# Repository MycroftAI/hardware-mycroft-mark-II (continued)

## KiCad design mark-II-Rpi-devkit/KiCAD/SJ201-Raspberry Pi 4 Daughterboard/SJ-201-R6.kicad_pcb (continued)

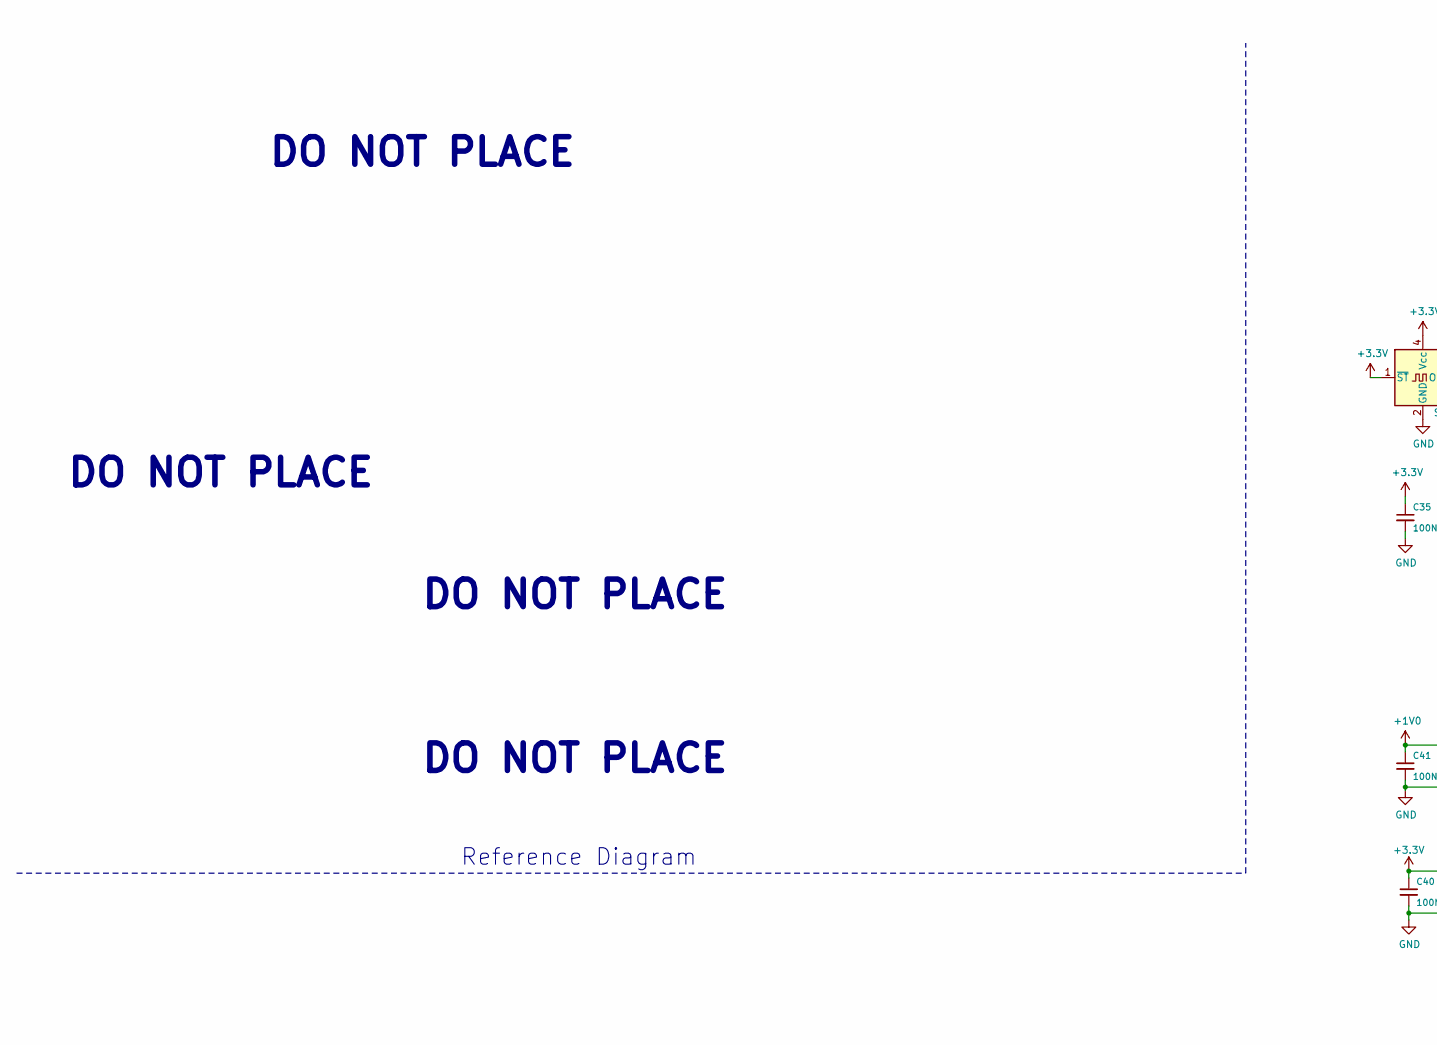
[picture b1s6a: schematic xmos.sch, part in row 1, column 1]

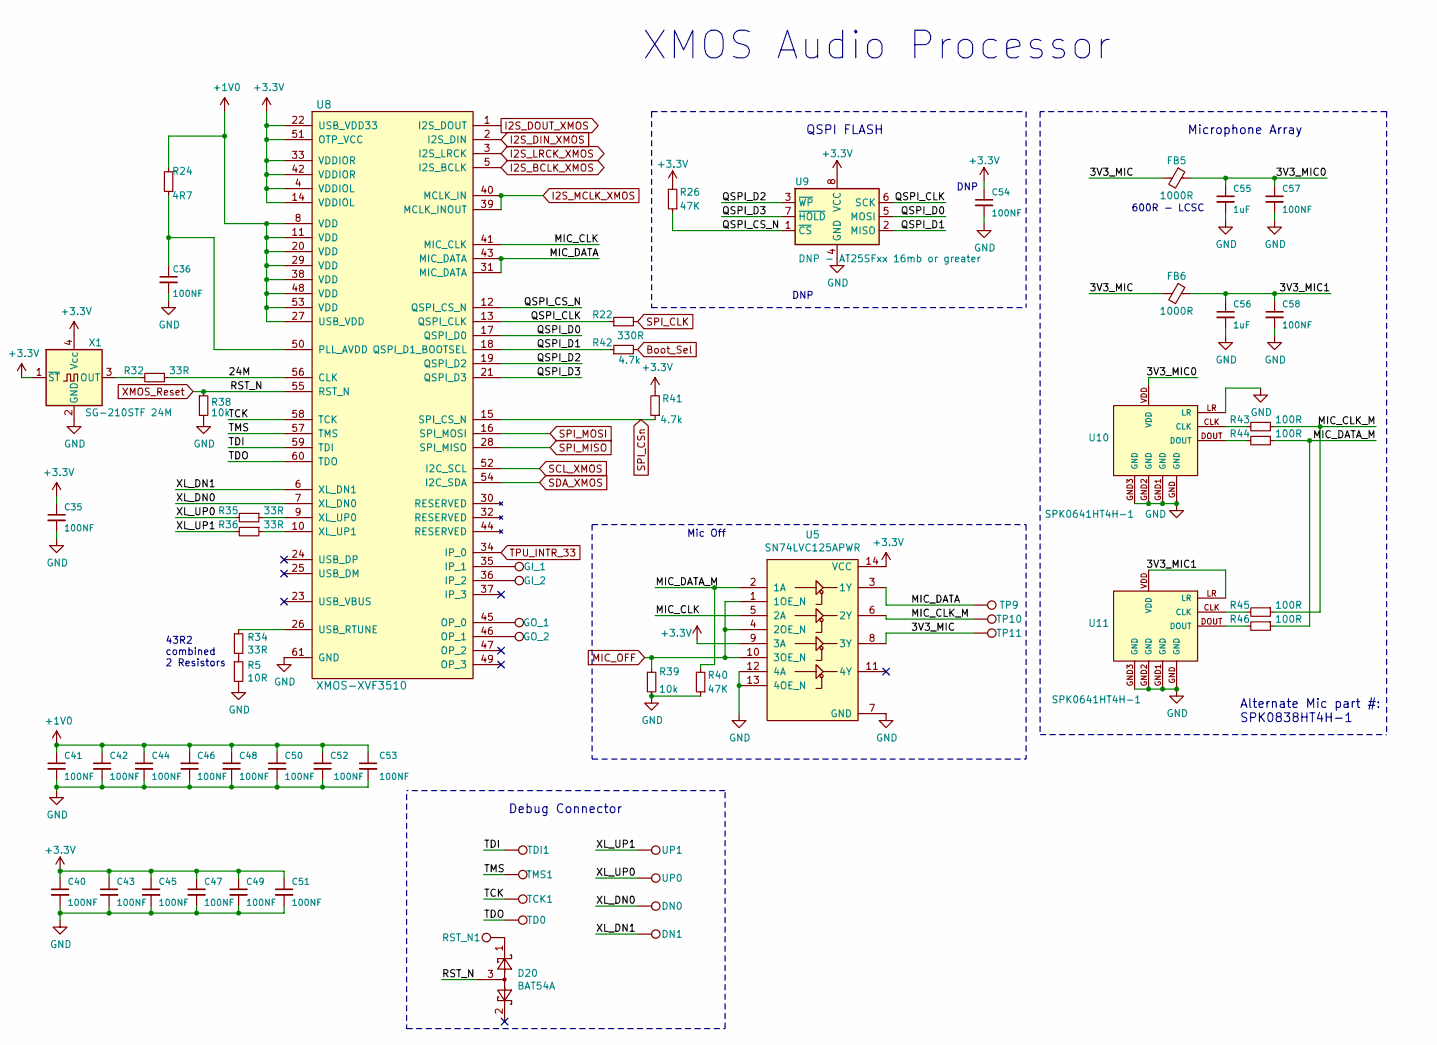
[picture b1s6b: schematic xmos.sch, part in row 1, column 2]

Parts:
C35, C36, C40, C41, C42, C43, C44, C45, C46, C47, C48, C49, C50, C51, C52, C53, C54, C57, C58: 100NF; C_0402_1005Metric; MPN CC0402KRX7R8BB104; LCSC C1525
C55, C56: 1uF; C_0402_1005Metric; MPN CL05A105KA5NQNC; LCSC C52923
D20: BAT54A; SOT-23; MPN BAT54ALT1G; LCSC C179724
DN0, DN1: TestPoint; TestPoint_Pad_D1.0mm; MPN DNP
FB5: 1000R; R_0805_2012Metric; MPN MPZ1608S102ATA00; LCSC C1017
FB6: 1000R; R_0805_2012Metric; PartNum MPZ1608S102ATA00; LCSC C1017
GI_1, GI_2: TestPoint; TestPoint_Pad_D2.0mm; MPN DNP
GO_1, GO_2: TestPoint; TestPoint_Pad_D2.0mm; MPN DNP
R5: 10R; R_0402_1005Metric; MPN 0402WGF100JTCE; LCSC C25077
R22: 330R; R_0402_1005Metric; MPN RC0402FR-07330RL; LCSC C25104
R24: 4R7; R_0603_1608Metric; MPN RC0402FR-074R7L; LCSC C23164
R26: 47K; R_0402_1005Metric; MPN 0402WGF4702TCE; LCSC C25792
R32, R34, R35, R36: 33R; R_0402_1005Metric; MPN 0402WGF330JTCE; LCSC C25105
R38, R39: 10k; R_0402_1005Metric; MPN RC0402FR-0710KL; LCSC C25744
R40: 47K; R_0402_1005Metric; MPN RC0402JR-0747KL; LCSC C25792
R41, R42: 4.7k; R_0402_1005Metric; MPN 0402WGF4701TCE; LCSC C25900
R43, R44, R45, R46: 100R; R_0402_1005Metric; MPN 0402WGF1000TCE; LCSC C25076
RST_N1: TestPoint; TestPoint_Pad_D2.0mm; MPN DNP
TCK1: TestPoint; TestPoint_Pad_D1.0mm; MPN DNP
TD0: TestPoint; TestPoint_Pad_D1.0mm; MPN DNP
TDI1: TestPoint; TestPoint_Pad_D1.0mm; MPN DNP
TMS1: TestPoint; TestPoint_Pad_D1.0mm; MPN DNP
TP9, TP10, TP11: TestPoint; TestPoint_Pad_D2.0mm; MPN DNP
U5: SN74LVC125APWR; TSSOP-14_4.4x5mm_P0.65mm; MPN SN74LVC125APWR; LCSC C7813
U8: XMOS-XVF3510; QFN-60-1EP_7x7mm_P0.4mm_EP5.6x5.6mm; MPN XVF3510-QF60-C
U9: DNP - AT25SFxx 16mb or greater; SOIC-8_5.23x5.23mm_P1.27mm; MPN AT25SF161-SHD-T-DNP; LCSC C93710-DNP
U10, U11: SPK0641HT4H-1; HCLGA-MP34DT05; MPN SPK0641HT4H-1; Digikey 423-1425-1-ND
UP0, UP1: TestPoint; TestPoint_Pad_D1.0mm; MPN DNP
X1: SG-210STF 24M; Oscillator_SMD_SeikoEpson_SG8002CE-4Pin_3.2x2.5mm; MPN SG-210STF 24.0000ML3; LCSC C32528

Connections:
+1V0: C41.1, C42.1, C44.1, C46.1, C48.1, C50.1, C52.1, C53.1, R24.2, U8.8 (VDD), U8.11 (VDD), U8.20 (VDD), U8.27 (USB_VDD), U8.29 (VDD), U8.38 (VDD), U8.48 (VDD), U8.53 (VDD); also elsewhere on the board
/xmos/3V3_MIC: FB5.2, FB6.2, TP11.1, U5.8 (3Y)
/xmos/3V3_MIC0: C55.1, C57.1, FB5.1, U10.VDD
/xmos/3V3_MIC1: C56.1, C58.1, FB6.1, U11.LR, U11.VDD
/xmos/24M: R32.1, U8.56 (CLK)
/xmos/MIC_CLK: U5.5 (2A), U8.41 (MIC_CLK)
/xmos/MIC_CLK_M: R43.1, R45.1, TP10.1, U5.6 (2Y)
/xmos/MIC_DATA: TP9.1, U5.3 (1Y), U8.31 (MIC_DATA), U8.43 (MIC_DATA)
/xmos/MIC_DATA_M: R40.2, R44.1, R46.1, U5.2 (1A)
/xmos/QSPI_CLK: R22.1, U8.13 (QSPI_CLK), U9.6 (SCK)
/xmos/QSPI_CS_N: R26.1, U8.12 (QSPI_CS_N), U9.1 (~CS)
/xmos/QSPI_D0: U8.17 (QSPI_D0), U9.5 (MOSI)
/xmos/QSPI_D1: R42.1, U8.18 (QSPI_D1_BOOTSEL), U9.2 (MISO)
/xmos/QSPI_D2: U8.19 (QSPI_D2), U9.3 (~WP)
/xmos/QSPI_D3: U8.21 (QSPI_D3), U9.7 (~HOLD)
/xmos/TCK: TCK1.1, U8.58 (TCK)
/xmos/TDI: TDI1.1, U8.59 (TDI)
/xmos/TDO: TD0.1, U8.60 (TDO)
/xmos/TMS: TMS1.1, U8.57 (TMS)
/xmos/XL_DN0: DN0.1, U8.7 (XL_DN0)
/xmos/XL_DN1: DN1.1, U8.6 (XL_DN1)
/xmos/XL_UP0: R35.2, UP0.1
/xmos/XL_UP1: R36.2, UP1.1
Boot_Sel: R42.2; also elsewhere on the board
GND: C35.2, C36.2, C40.2, C41.2, C42.2, C43.2, C44.2, C45.2, C46.2, C47.2, C48.2, C49.2, C50.2, C51.2, C52.2, C53.2, C54.2, C55.2, C56.2, C57.2, C58.2, R5.2, R38.2, R39.2, R40.1, U5.7 (GND), U5.12 (4A), U5.13 (4OE_N), U8.61 (GND), U9.4 (GND), U10.GND, U10.GND1 (GND), U10.GND2 (GND), U10.GND3 (GND), U10.LR, U11.GND, U11.GND1 (GND), U11.GND2 (GND), U11.GND3 (GND), X1.2 (GND); also elsewhere on the board
GPIO25: R39.1, U5.1 (1OE_N), U5.4 (2OE_N), U5.10 (3OE_N); also elsewhere on the board
I2S_BCLK_XMOS: U8.5 (I2S_BCLK); also elsewhere on the board
I2S_DIN_PI: U8.1 (I2S_DOUT); also elsewhere on the board
I2S_DIN_XMOS: U8.2 (I2S_DIN); also elsewhere on the board
I2S_LRCK_AMP: U8.3 (I2S_LRCK); also elsewhere on the board
I2S_MCLK_XMOS: U8.39 (MCLK_INOUT), U8.40 (MCLK_IN); also elsewhere on the board
unnamed: C36.1, R24.1, U8.50 (PLL_AVDD)
unnamed: D20.1, RST_N1.1
unnamed: GI_1.1, U8.35 (IP_1)
unnamed: GI_2.1, U8.36 (IP_2)
unnamed: GO_1.1, U8.45 (OP_0)
unnamed: GO_2.1, U8.46 (OP_1)
unnamed: R32.2, X1.3 (OUT)
unnamed: R34.1, U8.26 (USB_RTUNE)
unnamed: R5.1, R34.2
unnamed: R35.1, U8.9 (XL_UP0)
unnamed: R36.1, U8.10 (XL_UP1)
unnamed: R43.2, U10.CLK
unnamed: R44.2, U10.DOUT
unnamed: R45.2, U11.CLK
unnamed: R46.2, U11.DOUT
SCL: U8.52 (I2C_SCL); also elsewhere on the board
SDA: U8.54 (I2C_SDA); also elsewhere on the board
SPI_CLK: R22.2; also elsewhere on the board
SPI_CSn: R41.1, U8.15 (SPI_CS_N); also elsewhere on the board
SPI_MISO: U8.28 (SPI_MISO); also elsewhere on the board
SPI_MOSI: U8.16 (SPI_MOSI); also elsewhere on the board
TPU_INTR_33: U8.34 (IP_0); also elsewhere on the board
XMOS_Reset: D20.3, R38.1, U8.55 (RST_N); also elsewhere on the board

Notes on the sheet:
DO NOT PLACE
Reference Diagram
XMOS Audio Processor
QSPI FLASH
Debug Connector
Microphone Array
Alternate Mic part #: SPK0838HT4H-1
Mic Off
600R - LCSC
43R2 combined 2 Resistors
DNP

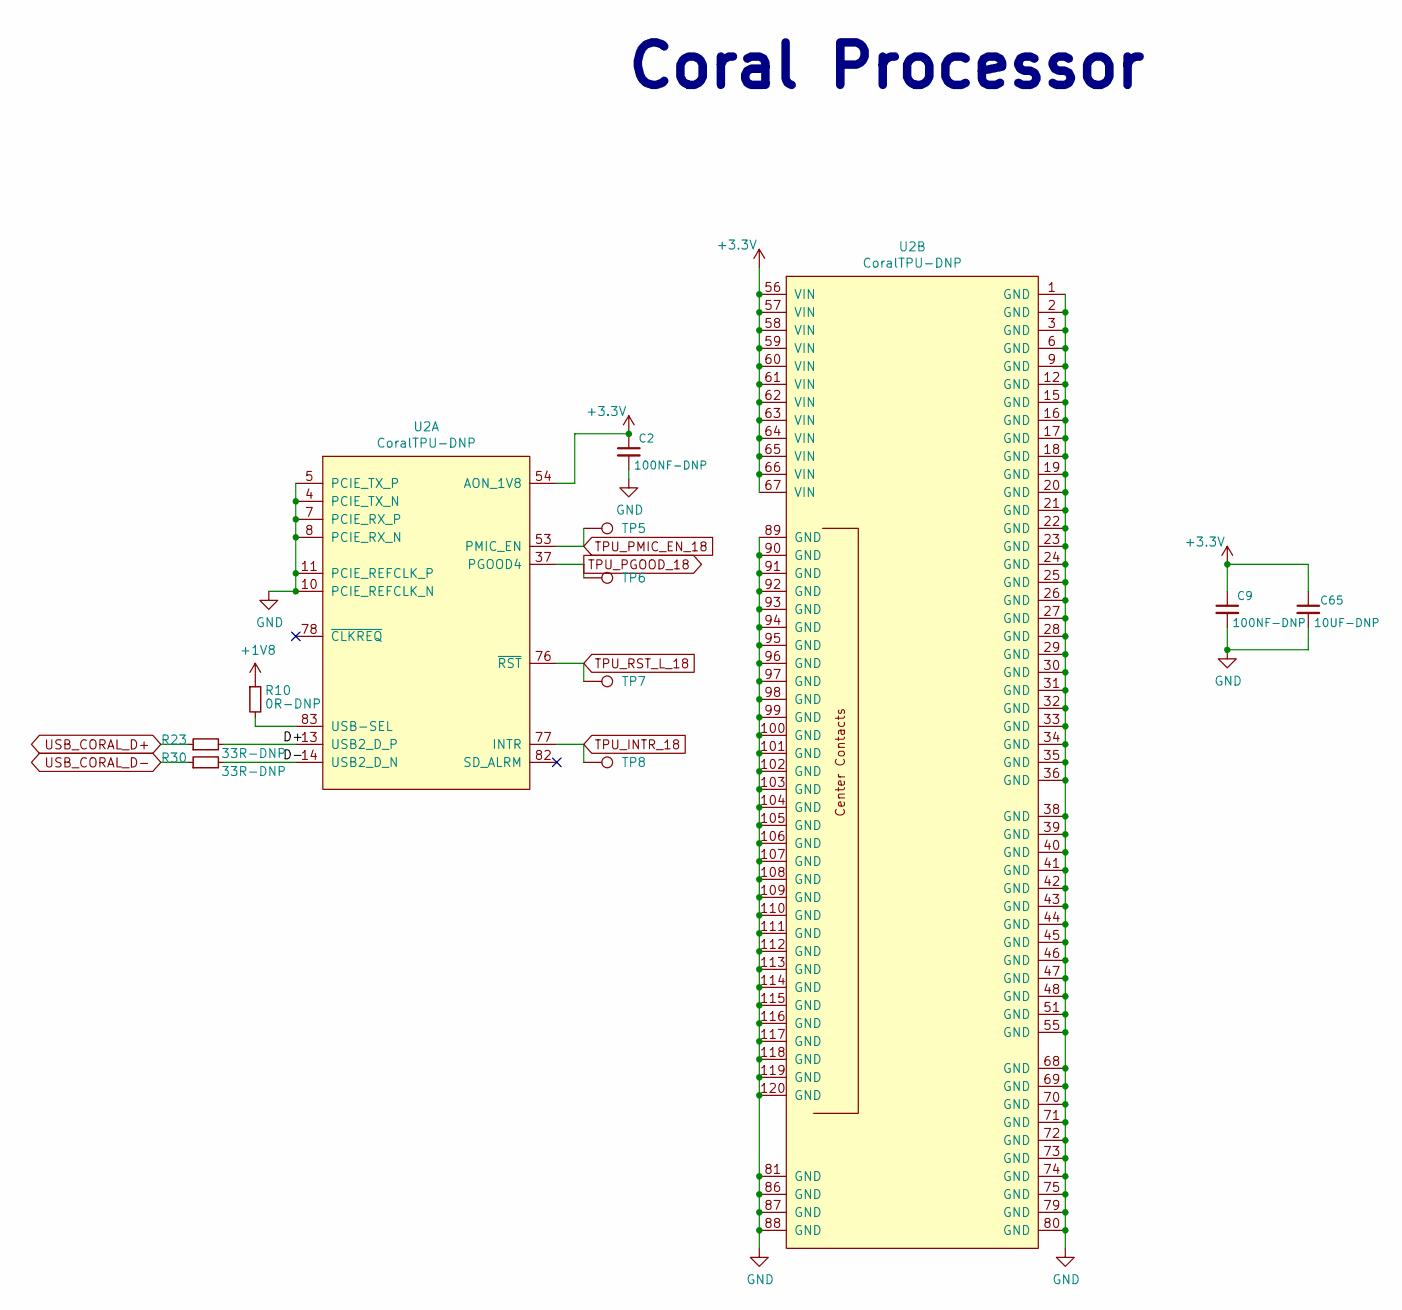
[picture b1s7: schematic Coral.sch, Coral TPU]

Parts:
C2, C9: 100NF-DNP; C_0402_1005Metric; MPN CC0402KRX7R8BB104-DNP; LCSC C1525-DNP
C65: 10UF-DNP; C_0402_1005Metric; MPN CC0402MRX5R5BB106-DNP; LCSC C15525-DNP
R10: 0R-DNP; R_0603_1608Metric; MPN 0603WAF0000T5E-DNP; LCSC C21189-DNP
R23, R30: 33R-DNP; R_0402_1005Metric; MPN 0402WGF330JTCE-DNP; LCSC C25105-DNP
TP5, TP6, TP7, TP8: TestPoint; TestPoint_Pad_D2.0mm; MPN DNP
U2: CoralTPU-DNP; CoralTPU

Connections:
+1V8: R10.1; also elsewhere on the board
/Coral Processor/D+: R23.2, U2.13 (USB2_D_P)
/Coral Processor/D-: R30.2, U2.14 (USB2_D_N)
GND: C2.2, C9.2, C65.2, U2.1 (GND), U2.2 (GND), U2.3 (GND), U2.4 (PCIE_TX_N), U2.5 (PCIE_TX_P), U2.6 (GND), U2.7 (PCIE_RX_P), U2.8 (PCIE_RX_N), U2.9 (GND), U2.10 (PCIE_REFCLK_N), U2.11 (PCIE_REFCLK_P), U2.12 (GND), U2.15 (GND), U2.16 (GND), U2.17 (GND), U2.18 (GND), U2.19 (GND), U2.20 (GND), U2.21 (GND), U2.22 (GND), U2.23 (GND), U2.24 (GND), U2.25 (GND), U2.26 (GND), U2.27 (GND), U2.28 (GND), U2.29 (GND), U2.30 (GND), U2.31 (GND), U2.32 (GND), U2.33 (GND), U2.34 (GND), U2.35 (GND), U2.36 (GND), U2.38 (GND), U2.39 (GND), U2.40 (GND), U2.41 (GND), U2.42 (GND), U2.43 (GND), U2.44 (GND), U2.45 (GND), U2.46 (GND), U2.47 (GND), U2.48 (GND), U2.51 (GND), U2.55 (GND), U2.68 (GND), U2.69 (GND), U2.70 (GND), U2.71 (GND), U2.72 (GND), U2.73 (GND), U2.74 (GND), U2.75 (GND), U2.79 (GND), U2.80 (GND), U2.81 (GND), U2.86 (GND), U2.87 (GND), U2.88 (GND), U2.89 (GND), U2.90 (GND), U2.91 (GND), U2.92 (GND), U2.93 (GND), U2.94 (GND), U2.95 (GND), U2.96 (GND), U2.97 (GND), U2.98 (GND), U2.99 (GND), U2.100 (GND), U2.101 (GND), U2.102 (GND), U2.103 (GND), U2.104 (GND), U2.105 (GND), U2.106 (GND), U2.107 (GND), U2.108 (GND), U2.109 (GND), U2.110 (GND), U2.111 (GND), U2.112 (GND), U2.113 (GND), U2.114 (GND), U2.115 (GND), U2.116 (GND), U2.117 (GND), U2.118 (GND), U2.119 (GND), U2.120 (GND); also elsewhere on the board
unnamed: R10.2, U2.83 (USB-SEL)
TPU_INTR_18: TP8.1, U2.77 (INTR); also elsewhere on the board
TPU_PGOOD_18: TP6.1, U2.37 (PGOOD4); also elsewhere on the board
TPU_PMIC_EN_18: TP5.1, U2.53 (PMIC_EN); also elsewhere on the board
TPU_RST_L_18: TP7.1, U2.76 (~RST); also elsewhere on the board
USB_CORAL_D+: R23.1; also elsewhere on the board
USB_CORAL_D-: R30.1; also elsewhere on the board

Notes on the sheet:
Coral Processor

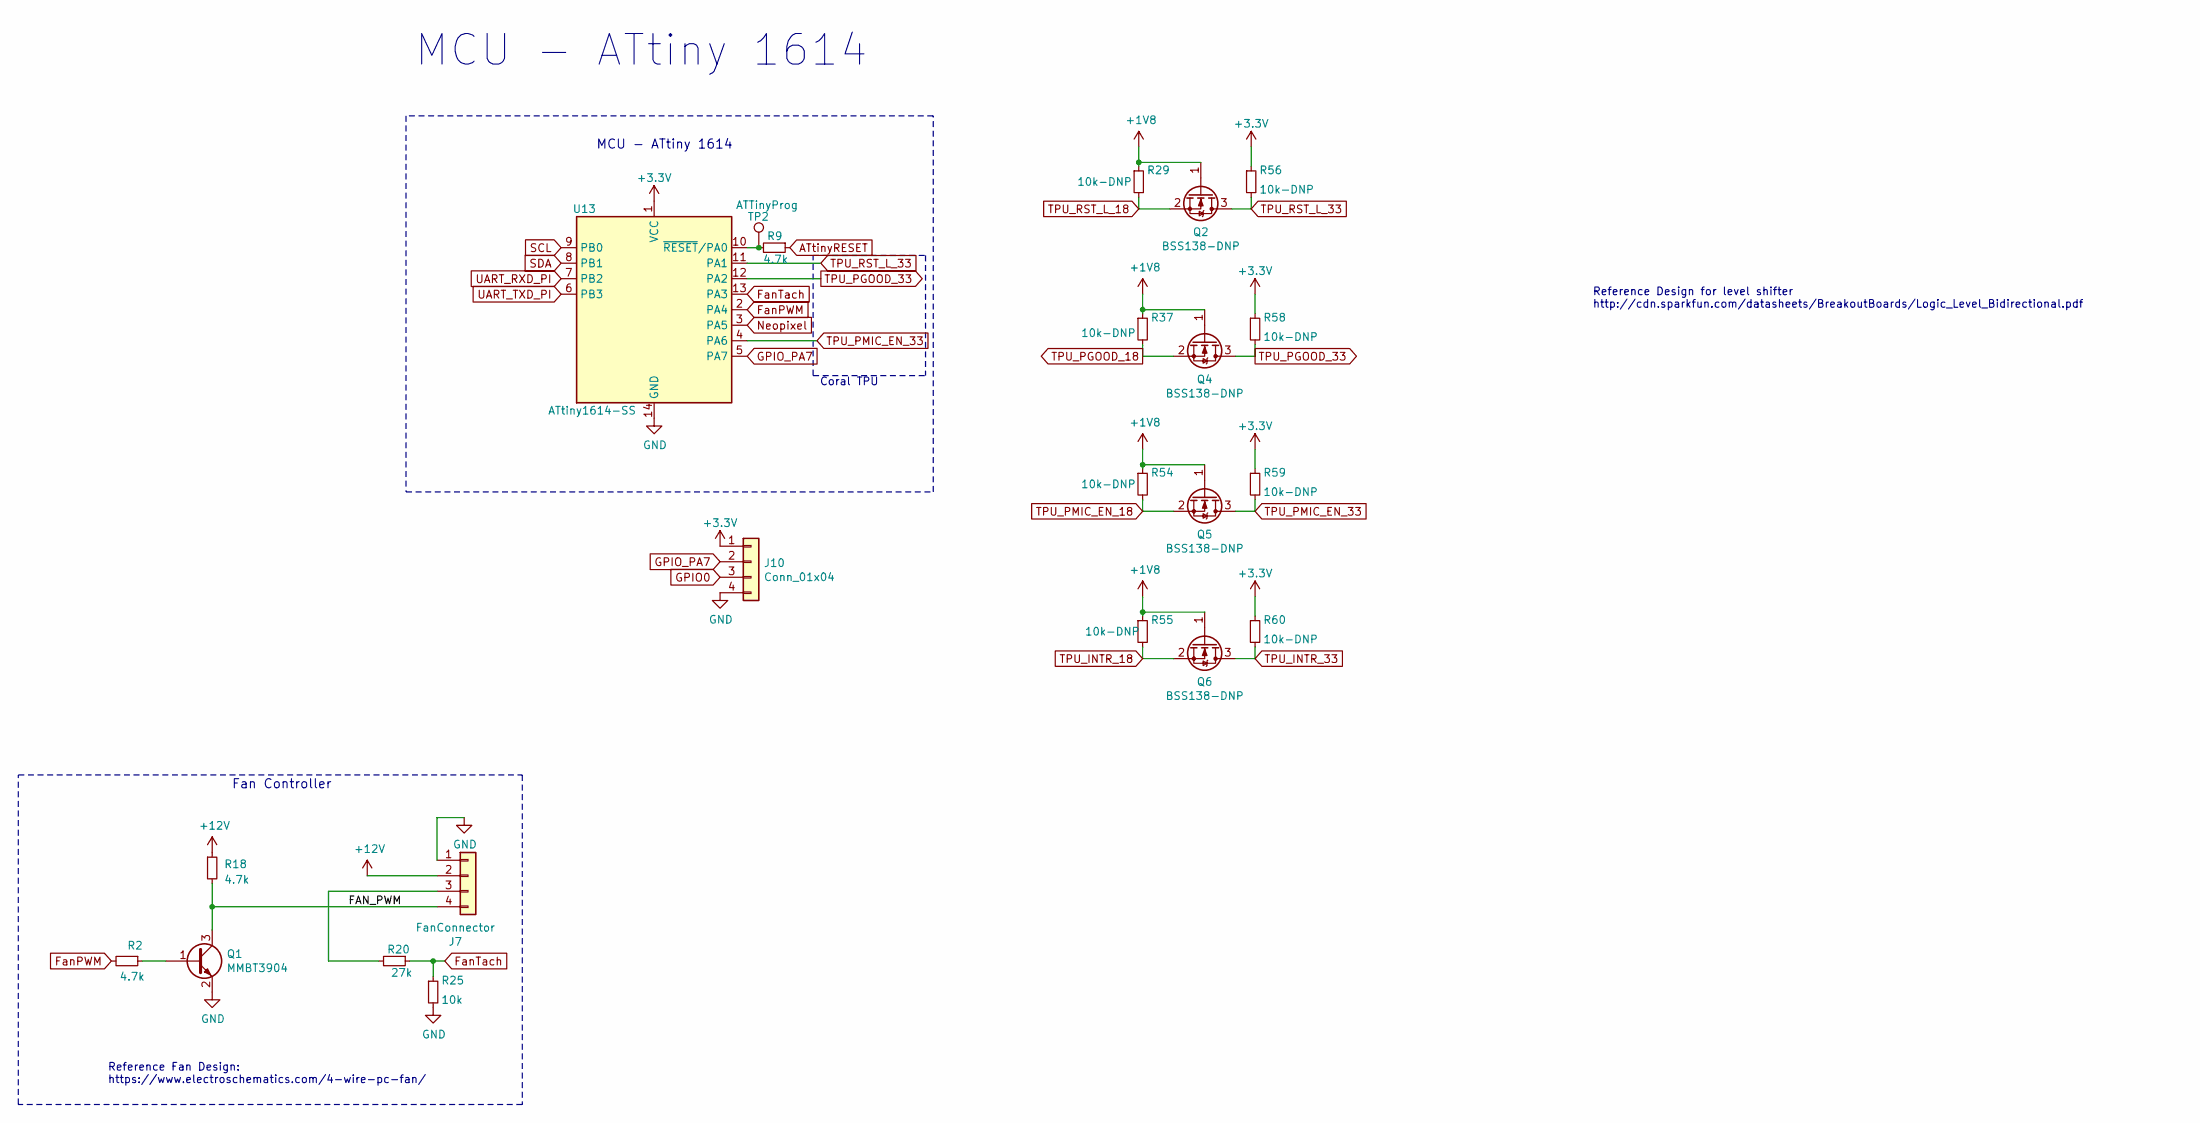
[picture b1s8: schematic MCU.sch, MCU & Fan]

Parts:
J7: FanConnector; FanPinHeader_1x04_P2.54mm_Vertical; MPN 744-81-04TG1B; LCSC C402775
J10: Conn_01x04; PinHeader_1x04_P2.54mm_Vertical; MPN DNP
Q1: MMBT3904; SOT-23; MPN MMBT3904; LCSC C382281
Q2, Q4, Q5, Q6: BSS138-DNP; SOT-23; MPN BSS138-DNP; LCSC C112239-DNP
R2, R9, R18: 4.7k; R_0402_1005Metric; MPN 0402WGF4701TCE; LCSC C25900
R20: 27k; R_0402_1005Metric; MPN 0402WGF2702TCE; LCSC C25771
R25: 10k; R_0402_1005Metric; MPN RC0402FR-0710KL; LCSC C25744
R29, R37, R55, R56, R58, R59: 10k-DNP; R_0402_1005Metric; MPN RC0402FR-0710KL-DNP; LCSC C25744-DNP
R54: 10k-DNP; R_0402_1005Metric; MPN RC0402FR-0710KL; LCSC C25744
R60: 10k-DNP; R_0402_1005Metric; MPN RC0402FR-0710KL-DNP; LCSC C25744
TP2: ATTinyProg; TestPoint_Pad_D2.0mm; MPN DNP
U13: ATtiny1614-SS; SOIC-14_3.9x8.7mm_P1.27mm; MPN ATTINY1614-SSNR; LCSC C481364

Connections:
+1V8: Q2.1 (G), Q4.1 (G), Q5.1 (G), Q6.1 (G), R29.1, R37.1, R54.1, R55.1; also elsewhere on the board
/MCU/FAN_PWM: J7.4, Q1.3 (C), R18.2
ATtinyRESET: R9.1; also elsewhere on the board
FanPWM: R2.2, U13.2 (PA4)
FanTach: R20.1, R25.1, U13.13 (PA3)
GND: J7.1, J10.4, Q1.2 (E), R25.2, U13.14 (GND); also elsewhere on the board
GPIO0: J10.3; also elsewhere on the board
GPIO_PA7: J10.2, U13.5 (PA7)
Neopixel: U13.3 (PA5); also elsewhere on the board
unnamed: J7.3, R20.2
unnamed: Q1.1 (B), R2.1
unnamed: R9.2, TP2.1, U13.10 (~RESET~/PA0)
PVDD: J7.2, R18.1; also elsewhere on the board
SCL: U13.9 (PB0); also elsewhere on the board
SDA: U13.8 (PB1); also elsewhere on the board
TPU_INTR_18: Q6.2 (S), R55.2; also elsewhere on the board
TPU_INTR_33: Q6.3 (D), R60.2; also elsewhere on the board
TPU_PGOOD_18: Q4.2 (S), R37.2; also elsewhere on the board
TPU_PGOOD_33: Q4.3 (D), R58.2, U13.12 (PA2)
TPU_PMIC_EN_18: Q5.2 (S), R54.2; also elsewhere on the board
TPU_PMIC_EN_33: Q5.3 (D), R59.2, U13.4 (PA6)
TPU_RST_L_18: Q2.2 (S), R29.2; also elsewhere on the board
TPU_RST_L_33: Q2.3 (D), R56.2, U13.11 (PA1); also elsewhere on the board
UART_RXD_PI: U13.7 (PB2); also elsewhere on the board
UART_TXD_PI: U13.6 (PB3); also elsewhere on the board

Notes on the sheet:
Coral TPU
MCU - ATtiny 1614
Reference Fan Design: https://www.electroschematics.com/4-wire-pc-fan/
Fan Controller
Reference Design for level shifter http://cdn.sparkfun.com/datasheets/BreakoutBoards/Logic_Level_Bidirectional.pdf

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
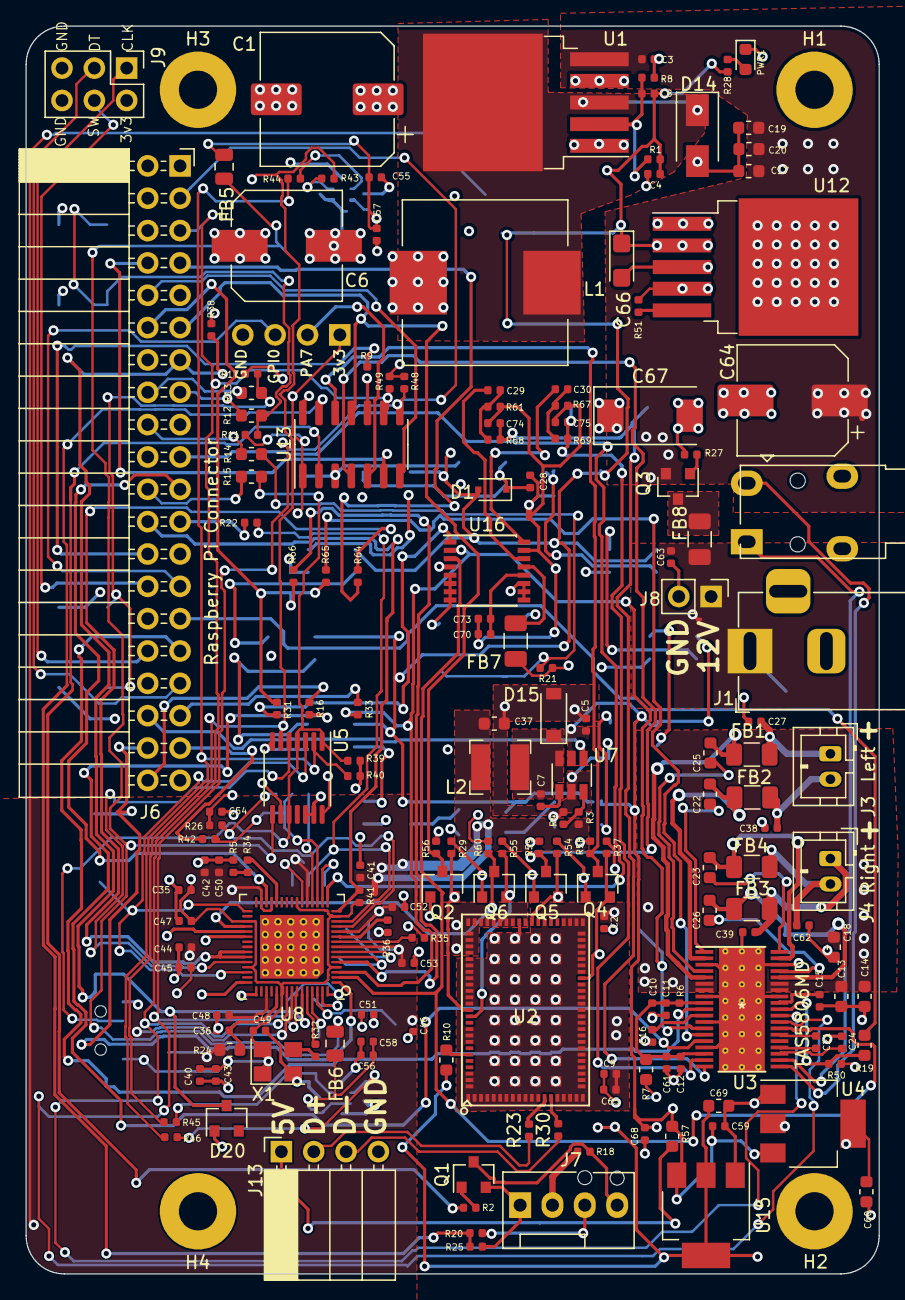
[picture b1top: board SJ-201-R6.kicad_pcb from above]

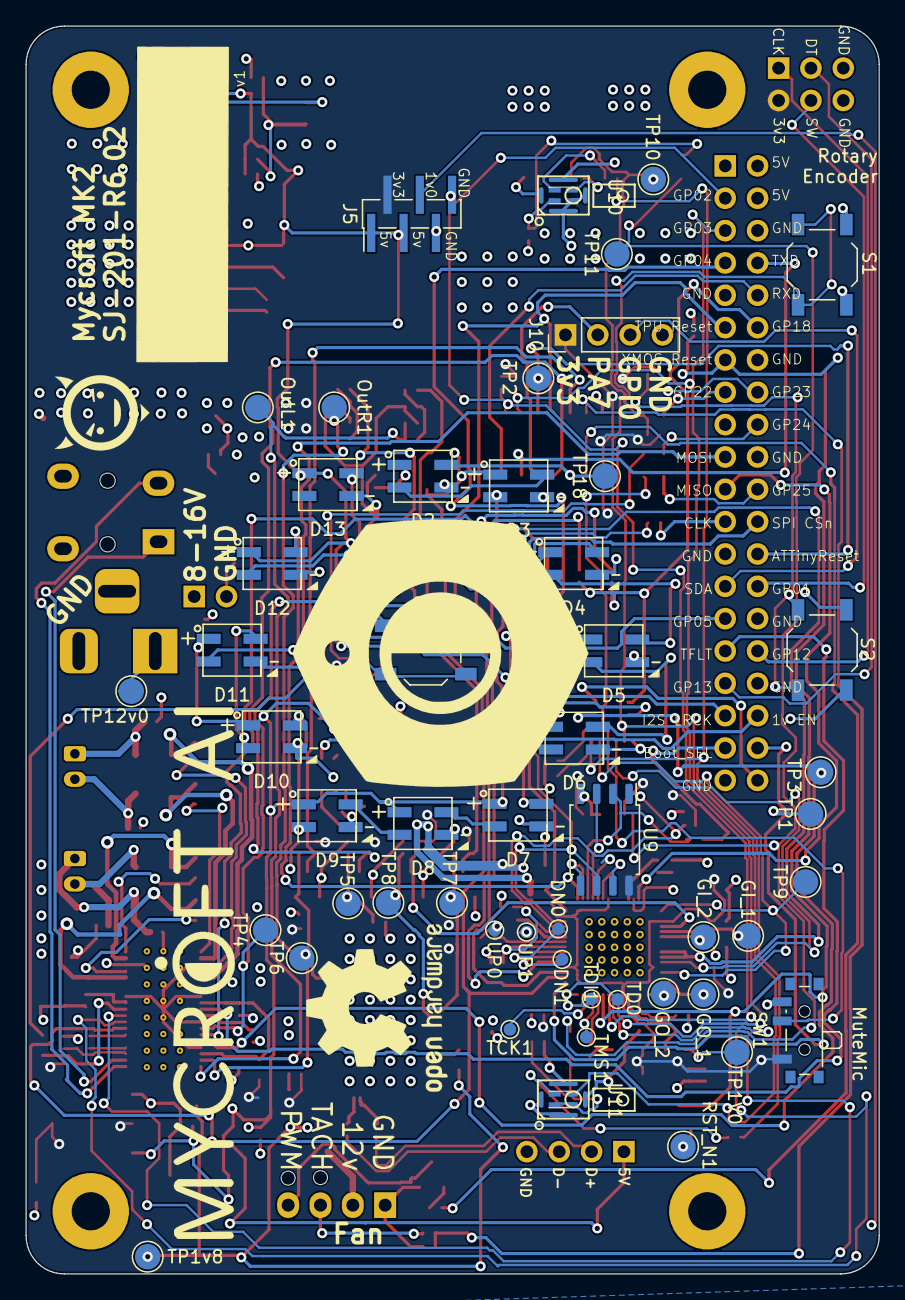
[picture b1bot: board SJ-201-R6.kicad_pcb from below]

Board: 4 copper layers, 67.0 x 98.0 mm, 235 parts (55 on the bottom side), 155 nets.

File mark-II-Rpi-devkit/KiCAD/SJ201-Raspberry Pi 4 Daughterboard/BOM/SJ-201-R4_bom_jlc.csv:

"Comment","Designator","Footprint","LCSC Part #"
"220uF/50V","C1","CP_Elec_10x10","C249500"
"1uF","C3,C4,C61,C15,C16,C21,C24,C55,C56","C_0402_1005Metric","C52923"
"330uF/25V","C6","CP_Elec_8x10.5","C286135"
"10nF","C7","C_0402_1005Metric","C15195"
"33NF","C8","C_0402_1005Metric","C1585"
"4.7UF","C10","C_0402_1005Metric","C23733"
"100NF","C17,C18","C_0603_1608Metric","C14663"
"220nF","C23,C26,C22,C25","C_0603_1608Metric","C21120"
"1NF","C27,C38,C39,C62","C_0402_1005Metric","C1523"
"10UF","C59,C5,C30,C32,C34,C65","C_0402_1005Metric","C15525"
"22UF","C60,C37,C19,C20,C13,C14","C_0603_1608Metric","C59461"
"100NF","C63,C12,C11,C28,C33,C31,C29,C40,C43,C45,C47,C49,C51,C53,C42,C44,C46,C48,C50,C52,C36,C35,C57,C58,C54,C41,C2,C9","C_0402_1005Metric","C1525"
"470UF/16V","C64","CP_Elec_8x10.5","C176671"
"1uF","C66","CP_EIA-3216-10_Kemet-I","C140386"
"470uF ","C67","CP_EIA-7343-15_Kemet-W","C156460"
"250mA/100V","D1","D_SOD-323F","C2128"
"WS2812B","D13,D9,D2,D12,D11,D10,D3,D4,D5,D6,D7,D8","LED_WS2812_Mini_3.5x3.5mm_P1.1mm","C527089"
"D_Schottky","D14","D_SMA","C22452"
"D_Schottky","D15","D_SOD-123","C8598"
"BAT54A","D20","SOT-23","C179724"
"TestPoint","DM3","TestPoint_Pad_D1.0mm","no_part_number"
"TestPoint","DP3","TestPoint_Pad_D1.0mm","no_part_number"
"1000R","FB5,FB6","R_0805_2012Metric","C1017"
"FB","FB8,FB1,FB4,FB3,FB2","R_1206_3216Metric","C29107"
"MountingHole","H1,H2,H3,H4","MountingHole_3mm_Pad","no_part_number"
"MountingHole","H5","mycroft_logo_graphic","no_part_number"
"MountingHole","H6","simon-jestor-logo","no_part_number"
"MountingHole","H7","mycroft_logo_words","no_part_number"
"Barrel_Jack","J1","BarrelJack_Horizontal","C381117"
"AudioJack2_Ground","J2","Jack_3.5mm_PJ-3210","C136686"
"SPK","J4,J3","JST_PH_B2B-PH-K_1x02_P2.00mm_Vertical","no_part_number"
"PowerTP","J5","PinHeader_1x06_P1.27mm_Vertical_SMD_Pin1Left","no_part_number"
"Raspberry_Pi_4","J6","PinSocket_2x20_P2.54mm_Horizontal","no_part_number"
"FanConnector","J7","FanPinHeader_1x04_P2.54mm_Vertical","no_part_number"
"Debug Connector","J10","PinHeader_2x09_P2.54mm_Vertical_SMD","no_part_number"
"USB-PinHeader","J13","PinSocket_1x04_P2.54mm_Horizontal","C225512"
"47uH","L1","L_Wuerth_HCI-1365","C429835"
"1.8UH ±30% 2.35A","L2","L_Bourns-SRN4018","no_part_number"
"Logo_Open_Hardware_Small","OpenHardware1","OSHW-Logo2_14.6x12mm_SilkScreen","no_part_number"
"LED_RED","PWR1","LED_0603_1608Metric","C2286"
"MMBT3904","Q1","SOT-23","C20526"
"AO3401A","Q3","SOT-23","C15127"
"10k","R1,R49,R48,R50,R29,R11,R21,R17,R39","R_0402_1005Metric","C25744"
"4.7k","R2,R18,R9,R41,R42","R_0402_1005Metric","C25900"
"47k","R3","R_0402_1005Metric","C25792"
"200k","R4","R_0402_1005Metric","C25764"
"10R","R5","R_0402_1005Metric","C25077"
"120k","R6","R_0402_1005Metric","C25750"
"3.3K","R8,R51","R_0402_1005Metric","C25890"
"0R","R16,R47,R53,R62,R33","R_0402_1005Metric","C17168"
"27k","R20","R_0402_1005Metric","C25771"
"330R","R22","R_0402_1005Metric","C25104"
"47K","R23,R26,R40","R_0402_1005Metric","C25792"
"4R7","R24","R_0603_1608Metric","C23164"
"100k","R27,R30","R_0402_1005Metric","C25741"
"680R","R28","R_0402_1005Metric","C25130"
"2.7k","R31","R_0603_1608Metric","C13167"
"0R - DNP","R37,R25,R57","R_0603_1608Metric","no_part_number"
"100R","R43,R44,R45,R46","R_0402_1005Metric","C25076"
"0R - DNP","R52,R63","R_0402_1005Metric","no_part_number"
"0R","R55,R54,R7,R12,R13,R14,R15,R19,R10","R_0603_1608Metric","C21189"
"33R","R64,R65,R66,R34,R36,R35,R32","R_0402_1005Metric","C25105"
"Button","S1,S3,S2","SW_SPST_TL3342","C318884"
"MuteMic","SW1","SW_SPDT_PCM12","C221841"
"TestPoint","TP1_0V1","TestPoint_Pad_D2.0mm","no_part_number"
"ATTinyProg","TP2","TestPoint_Pad_D2.0mm","no_part_number"
"TestPoint","TP3,TP1,TP4,TP8,TP7,TP6,TP5","TestPoint_Pad_D1.0mm","no_part_number"
"TestPoint","TP12v1","TestPoint_Pad_D2.0mm","no_part_number"
"TestPoint","TP18,TP9,TP10,TP11","TestPoint_Pad_D2.0mm","no_part_number"
"XL4501E1","U1","TO-263-5_TabPin3","C73025"
"CoralTPU","U2","CoralTPU","no_part_number"
"TAS5806MD","U3","TAS5806MDDCPR","no_part_number"
"AMS1117-3.3","U4","SOT-223-3_TabPin2","C6186"
"SN74LVC125APWR","U5","TSSOP-14_4.4x5mm_P0.65mm","C7813"
"FE1.1s","U6","SSOP-28_3.9x9.9mm_P0.635mm","C9359"
"MP2359","U7","TSOT-23-6","C14259"
"XMOS-XVF3510","U8","QFN-60-1EP_7x7mm_P0.4mm_EP5.6x5.6mm-HandSolder","no_part_number"
"AT25SF161 16MBIT","U9","SOIC-8_5.23x5.23mm_P1.27mm","C93711"
"SPK0641HT4H-1","U10,U11","HCLGA-MP34DT05","no_part_number"
"TPS75933KTT","U12","TO-263-5_TabPin3","no_part_number"
"ATtiny1614-SS","U13","SOIC-14_3.9x8.7mm_P1.27mm","C481364"
"NC7NZ34K8XTR","U14","ON_Semi-NZ34-0-0-0","no_part_number"
"SG-210STF 24M","X1","Oscillator_SMD_SeikoEpson_SG8002CE-4Pin_3.2x2.5mm","C32528"
"12MHz","Y2","Crystal_SMD_3225-4Pin_3.2x2.5mm","C9002"

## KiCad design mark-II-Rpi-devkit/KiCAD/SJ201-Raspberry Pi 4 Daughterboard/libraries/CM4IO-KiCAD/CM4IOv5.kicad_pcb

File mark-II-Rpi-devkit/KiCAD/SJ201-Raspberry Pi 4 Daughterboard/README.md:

# SJ201 Datasheet - Rev 8

This board interfaces directly to the Raspberry Pi 4 via the 40-pin GPIO adding a high-quality speaker and microphone array, as well as LEDs and hardware inputs for non-voice interaction and feedback.

The part number SJ201 is derived from Mike’s “Simon Jester” alias in “The Moon is a Harsh Mistress”.

## About this Document

This Datasheet will contain all the relevant information for the manufacturing of the SJ201 including information about PCB design, PCB manufacturing process.

## Major Components
* Audio Front End (XMOS XVF3510) - for Microphone input processing
* 23W I2S Digital Amplifier (Texas Instruments TAS5806MD)
* 2 Digital MEMS Microphones ([Knowles SPK0641HT4H-1](https://www.digikey.com/en/products/detail/knowles/SPK0641HT4H-1/8573345))
* 12 RGB LEDs (WorldSemi WS2812B-MINI)
* 3 momentary buttons (volume up, volume down, action)
* 1 toggle switch (mic mute)
* ATtiny1614 - control LEDs, other I/O

## Hardware Notes

- The SJ201 is plugged into the GPIO header of the Raspberry Pi 4 board.
- The pins required for the operation of the Raspberry Pi 4 MIPI and CSI are not used on the SJ201 GPIO header. The display and camera do not connect to the SJ201.
- The barrel jack on the SJ201 requires a 12V, 3A regulated DC input.

## Software Notes
- SHTDN (GPIO pin GPIO5) must be set high to enable the audio amplifier.
- The TAS5806 outputs I2S to the XMOS chip. 

## Configuration options

### Default Use Case

The SJ201 is connected to a Raspberry Pi4 via the header. 

12V is supplied to the SJ201 via the barrel jack.

The SJ201 creates 5V using a 3A buck converter, which powers the Raspberry Pi.

The SJ201 creates 3.3V using a linear regulator, which powers the on-board devices.

4.4ohm, 5W speakers are connected to the JST connectors. [Note, in the current implementation the amplifier is capable of supplying 13W to each speaker, so volume must be limited in software to avoid damage.]

### Test Configuration Options

The J5 header serves as a test point for the 3.3V, 5V and 12V supplies. 

The J5 header can also be used to bypass the on-board buck converter and/or linear regulator.

The buck converter does not need to be turned off - it can tolerate an external supply. To completely disable it, lift the appropriate pin.

The 1.0V supply can be tested using Test Point TP1_0V1 near the XMOS IC.

## Design Notes

### Power Domains

The SJ201 is powered by an external 12V 3A DC supply (wall wart) via a barrel connector. The SJ201 has 4 voltage domains:

- VDD 12V externally supplied power

- PVDD 12V Analog Audio Power

- 5V  5V derived from VDD

- 3V  3.3V derived from 5V

- 1V  1.0V derived from 5V for the XMOS core

All power domains share a common ground.

- GND  Ground

### Microphone DSP

### Audio Amplifier

**Filterless modulation**  
We are using the TAS5806, in a "filterless amplifier" design. This is lower cost than using a true LC filter for each output, but can be susceptible to large EMI output if not done properly. This can lead to failure to meet FCC and other standards required for consumer electronics. The following design rules are intended to minimize EMI in the system.

**Speaker power**  
With a 4ohm speaker and a 12V supply, each channel can achieve ~13W. The speaker we're using is 4.4ohm, 5W max. The volume must be limited in software to avoid damaging the speaker.

## PCB Layout Checklist

Boxes marked 🗹 are for version 6.02 (also labeled R6 v2) of the KiCAD files.

### Layers - PCB checklist

Layer 1:  Main ICs, connectors and signal routing - Power (1.0v, PVDD 12v)

Layer 2:  GND

Layer 3:  Power (12V, 5V, 3V3)

Layer 4:  Buttons, LEDs, signal routing (this layer faces upwards on device) 

### Power - PCB checklist

#### External Power Supply (VDD)

1. Barrel jack is centered on 10.6mm from the board edge.

2. Ferrite bead close to barrel jack to reduce EMI transmission along power cord to wall
   - Spec'd to handle 12V 3A

3. AO3401A MOSFET to protect against reverse voltage (i.e. user plugs in a non-standard external power supply with GND on the center pin instead of on the outside of the barrel connector.)

4. Low resistance traces for VDD and GND connecting to power planes.

#### Analog Audio Power (PVDD)

1. PVDD does not contain loops (areas of PVDD that enclose non-PVDD areas)

2. PVDD does not contain narrow antenna-like features.

3. PVDD is primarily located on layer 3

4. PVDD connects to layer 1 traces through multiple vias for lower resistance

5. See Audio Amplifier for additional considerations

#### 5V power

XL Semiconductor's XL4015 buck converter is used to generate 5V at up to 5A from the barrel jack power. This part supports a minimum input voltage of 8V and a max of 36V. 

🗹  <http://www.xlsemi.com/datasheet/XL4015%20datasheet.pdf>

🗹  R1 and R8 are 1% tolerance (these set the output voltage. 10% resistors could result in an output range of 4.4V - 5.9V.)

#### 3.3V power

A linear regulator is used to derive 3.3V from 5V.

-   AZ1117CH-3.3

-   <https://www.diodes.com/assets/Datasheets/AZ1117C.pdf> 

### Microphones (MP34DT05-A)- PCB checklist

🗹  <https://www.st.com/content/ccc/resource/technical/document/datasheet/group3/c7/90/d3/f6/b7/e7/40/c8/DM00415595/files/DM00415595.pdf/jcr:content/translations/en.DM00415595.pdf> 

🗹  Power supply decoupling capacitors (100 nF ceramic, 1 μF ceramic) should be placed as near as possible to pin 1 of the device (common design practice). 

🗹  The L/R pin must be connected to Vdd or GND (refer to Table 6. L/R channel selection).

### LED (WS2812B-Mini)- PCB checklist

🗹  <https://datasheet.lcsc.com/szlcsc/2005251033_Worldsemi-WS2812B-Mini_C527089.pdf>

### Power on Reset - PCB checklist

-   <https://www.onsemi.com/pub/Collateral/NCP302-D.PDF> 

-   ~~This circuit monitors multiple power supply rails for undervoltage conditions. If any of the three power supplies are in an undervoltage condition, the NCP302 reset output will be immediately set to an active low level. All three power supplies must be above their minimum voltage levels for the NCP302 reset output to generate a "Power Good" level (Reset Output = Power Supply 1 or VP).~~ Replaced by Raspberry Pi control for startup routine.

### SG-210STF 24MHz clock - PCB checklist

🗹 Use recommended pad layout per datasheet.

-   <https://support.epson.biz/td/api/doc_check.php?mode=dl&lang=en&Parts=SG-210STF> 

### XMOS XVF3510 - PCB checklist 

Datasheets:

-   <https://www.xmos.com/documents/vocalfusionavs>

From page 26-27 of the XMOS VocalFusion XVF3510 datasheet (dated 2019-10-22).

10.1 SCHEMATICS DESIGN CHECK LIST

10.1.1. POWER SUPPLIES

🗹 The VDD (core) supply ramps monotonically (rises constantly) from 0V to its final value (0.95V - 1.05V) within 10ms (Section 6.1).

🗹 The VDD (core) supply is capable of supplying 1400mA (Section 6.1).

🗹 PLL_AVDD is filtered with a low pass filter, for example an RC filter, (Section 6.1)

10.1.2. POWER SUPPLY DECOUPLING

🗹 The design has multiple decoupling capacitors per supply, for example less than 12 402 or 0603 size surface mount capacitors of 100nF in value, per supply (Section 6.1).

🗹 A bulk decoupling capacitor of at least 10uF is placed on each supply (Section 6.1).

10.1.3. POWER ON RESET

🗹 The RST_N pins are asserted (low) until all supplies are good. There is enough time between VDDIO power good and RST_N to allow any boot flash to settle (Section 6.1).

10.1.4. CLOCKS

🗹 The CLK input pin is supplied with a clock with monotonic rising edges and low jitter.

🗹 A 24MHz reference clock must be connected to the CLK pin for all implementations.

🗹 MCLK_INOUT is connected to MCLK_IN via a PCB trace outside the device

🗹 All clock signals (CLK, MIC_CLK, QSPI_CLK, SPI_CLK, MCLK_IN, MCLK_INOUT, BCLK, LRCLK) and other audio signals must be routed well following high speed digital design guidelines, and may need buffering.

10.1.5. BOOT

~~🗹 To boot from QSPI flash, QSPI_CS_N, QSPI_D0 .. QSPI_D3, QSPI_D1_BOOTSEL, QSPI_CLK are connected and QSPI_D1_BOOTSEL is connected to QSPI D1 pin on flash device or pulled low/left floating (Section 6.4).~~ Boot from Raspi

🗹 To boot from the local host processor through SPI, QSPI_D1_BOOTSEL must be pulled high and SPI_CS_N, SPI_MOSI and SPI_MISO must be connected.

10.1.6. MICROPHONES

🗹 Both MIC_DATA pins are connected to the PCB (Section 4.4).

10.1.7. JTAG AND DEBUGGING

🗹 You have decided as to whether you need an XSYS header or not (Section 7)

🗹 If you have not included an XSYS header, you have devised a method to program the SPI-flash (Section 7).

10.2 PCB LAYOUT DESIGN CHECK LIST

10.2.1. GROUND PLANE

🗹 Multiple vias (eg, 16) have been used to connect the ground paddle to the PCB ground plane. These minimize impedance and conduct heat away from the device. (Section 6.1)

🗹 Other than ground vias, there are no (or only a few) vias underneath or closely around the device. This creates a good, solid, ground plane.

10.2.2. POWER SUPPLY DECOUPLING

🗹 The decoupling capacitors are all placed close to a supply pin (Section 6.1).

🗹 The decoupling capacitors are spaced around the device (Section 6.1).

🗹 The ground side of each decoupling capacitor has a direct path back to the center ground of the device.

10.2.3. PLL_AVDD

🗹 The PLL_AVDD filter (especially the capacitor) is placed close to the PLL_AVDD pin (Section 6.1).

### Audio Amplifier - PCB checklist

The following notes are related to the PCB layout wrt the TAS5806. We also used the MAX9744 design notes, as that was the amplifier for the first iteration and the notes are generally applicable.

1. 🗹 Ferrite bead close to 12V barrel connector
   - "It is sometimes helpful to insert RF chokes in series with the power supplies for the amplifier. Properly placed, they can confine high-frequency transient currents to local loops near the amplifier, instead of being conducted for long distances down the power supply wires." [Ref 1]

2. 🗹 Compact LC circuit from output of amplifier to JST speaker connectors
   - "the entire LC filter (including the speaker wiring) should be laid out as compactly as possible, and kept close to the amplifier." [Ref 1]

3. 🗹 Make speaker connections parallel and close to minimize area and therefore the "antenna" created
   - "Traces for current drive and return paths should be kept together to minimize loop areas." [Ref 1]

4. 🗹 Speaker wires from JST to speaker element are twisted pair and less than 10cm long.
   - "to minimize loop areas ... using twisted pairs for the speaker wires is helpful)" [Ref 1]

5. 🗹 Connect PGND to GND at a single point on the PCB. [Ref 3, p23]

6. 🗹 Connect all VDD power supplies together and bypass with a 1uF cap to GND. [Ref 3, p23]

7. 🗹 Place a bulk capacitor between PVDD and PGND. [Ref 3, p23]

8. 🗹 Use large, low-resistance output traces to speaker filters and JST connectors. [Ref 3, p23]

9. 🗹 Use large traces for the power-supply to PVDD and PGND. [Ref 3, p23]

10. 🗹 Thermal pad (area fill exposed copper) under amplifier on layer 1. [Ref 3, p23]
   - There should be no solder-mask in this area. [TODO: verify]

11. 🗹 Connect thermal pad on layer 1 to PGND on layer 2 using multiple vias. PGND area as large as practical for better heat dissipation. [Ref 3, p23]

## Production Checklist

WS2812 Mini

- [] This has to be baked for 48 hours at the baking temperature of 70-75℃ before being used. 

- [] Use up with 2 hours after taking out from oven.

- [] Please replace the unused LEDs into oven.

## References

1\. [Texas Instruments Class D Thermal Considerations](https://www.ti.com/lit/an/slaa880/slaa880.pdf?ts=1615242326443&ref_url=https%253A%252F%252Fwww.google.com%252F)

2\. [TAS5806MD data sheet](https://www.ti.com/lit/ds/symlink/tas5806md.pdf?ts=1615242375420&ref_url=https%253A%252F%252Fwww.ti.com%252Fproduct%252FTAS5806MD)

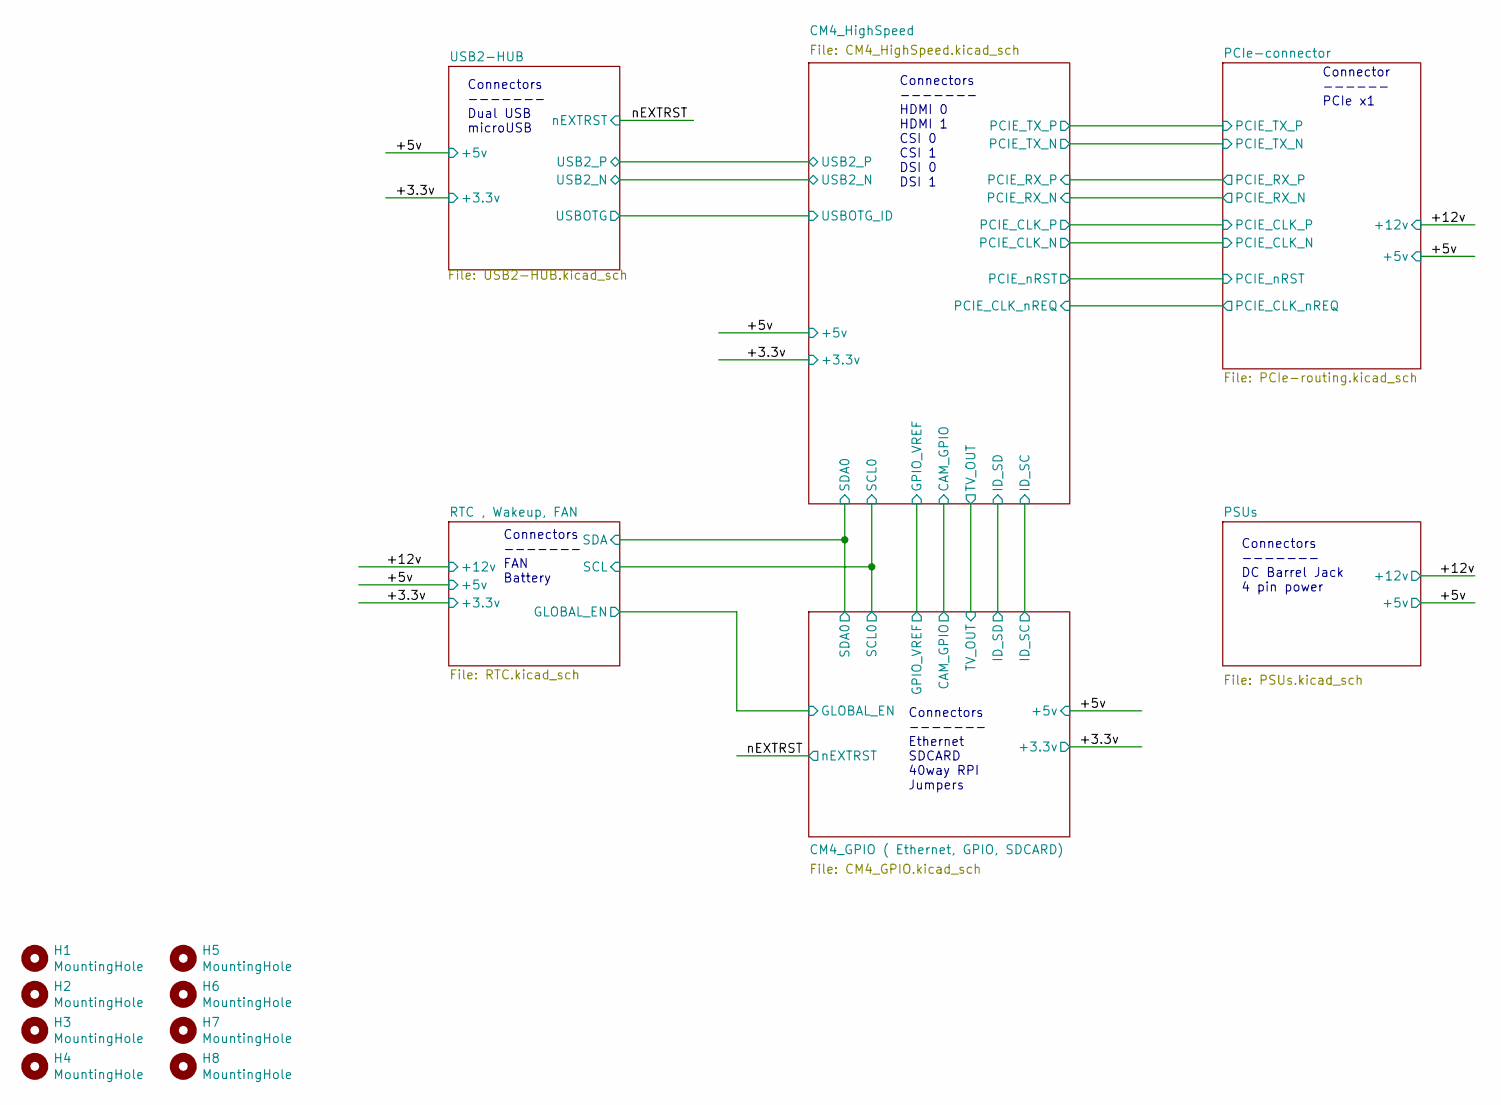
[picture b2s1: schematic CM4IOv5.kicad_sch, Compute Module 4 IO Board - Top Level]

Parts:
H1, H2, H3, H4, H5, H6, H7, H8: MountingHole; MountingHole_2.7mm_M2.5; Part Description M2.5 mounting hole

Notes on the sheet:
Connectors ------- Dual USB microUSB
Connectors ------- FAN Battery
Connectors ------- HDMI 0 HDMI 1 CSI 0 CSI 1 DSI 0 DSI 1
Connectors ------- Ethernet SDCARD 40way RPI Jumpers
Connectors ------- DC Barrel Jack 4 pin power
Connector ------ PCIe x1
